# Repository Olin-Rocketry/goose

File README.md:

# G.O.O.S.E
**G**reat **O**verview **O**f **S**TM **E**lectronics

The overarching goal of this project is to establish the foundation for designing and coding boards with more advanced stm32f-series microcontrollers. These microcontrollers are arm-based, super common in industry and hobbyist projects, have a large community of support, and a ton of features avr chips don't have like:
- usb support
- real time clocks
- high clock speeds (>100Mhz)
- SDIO communication support
- debugging ports
- Direct Memory Access (DMA)

## Development Board
As a development board the primary focus is on testing new hardware (stm32, sensors, power-converts, communication lines, memory, etc). As a result, this board has a ton of pinouts for direct access to almost every pin on the stm32 and all of the communication ports. This board also has a wide voltage input range (3V3 to 14V) in order to allow for a variety of input sources (power supply, battery, usb port, etc). The following is a list of key components on the board.

- **Microcontroller**
	- STM32F401RCT6
- **Sensors**
	- IMU--BMI088
	- Magnetometer--LIS3MDLTR
	- Barometer--MS560702BA03-50
- **Non-Volatile Memory**
	- FM25L04B-G
- **Connection**
	- Micro-SD
	- Debugging/Programming Port 
	- Micro-USB
	- SPI, I2C, UART pinouts
	- Other pinouts
- **Power**
	- Input
		- 3V3 to 14V
	- Output
		- 5V (buck converter)
		- 3V3 (Low Droput Regulator)

## Schematic
The full schematic pdf view can be viewed [here](/hardware/dev_board.pdf)

## Kicad Parts & Footprints
Currently, most of the parts and footprints are located in a [personal library](https://github.com/wFairmanOlin/kicad_parts). I will transition the necessary files to the olin rocketry library when the project is closer to completion.

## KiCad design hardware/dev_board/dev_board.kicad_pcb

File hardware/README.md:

## Accessing Parts Folder 

For now, if you want to access the parts for this board, clone this [repo](https://github.com/wFairmanOlin/kicad_parts) and add a path pointing to `personal.lib` similar to this:

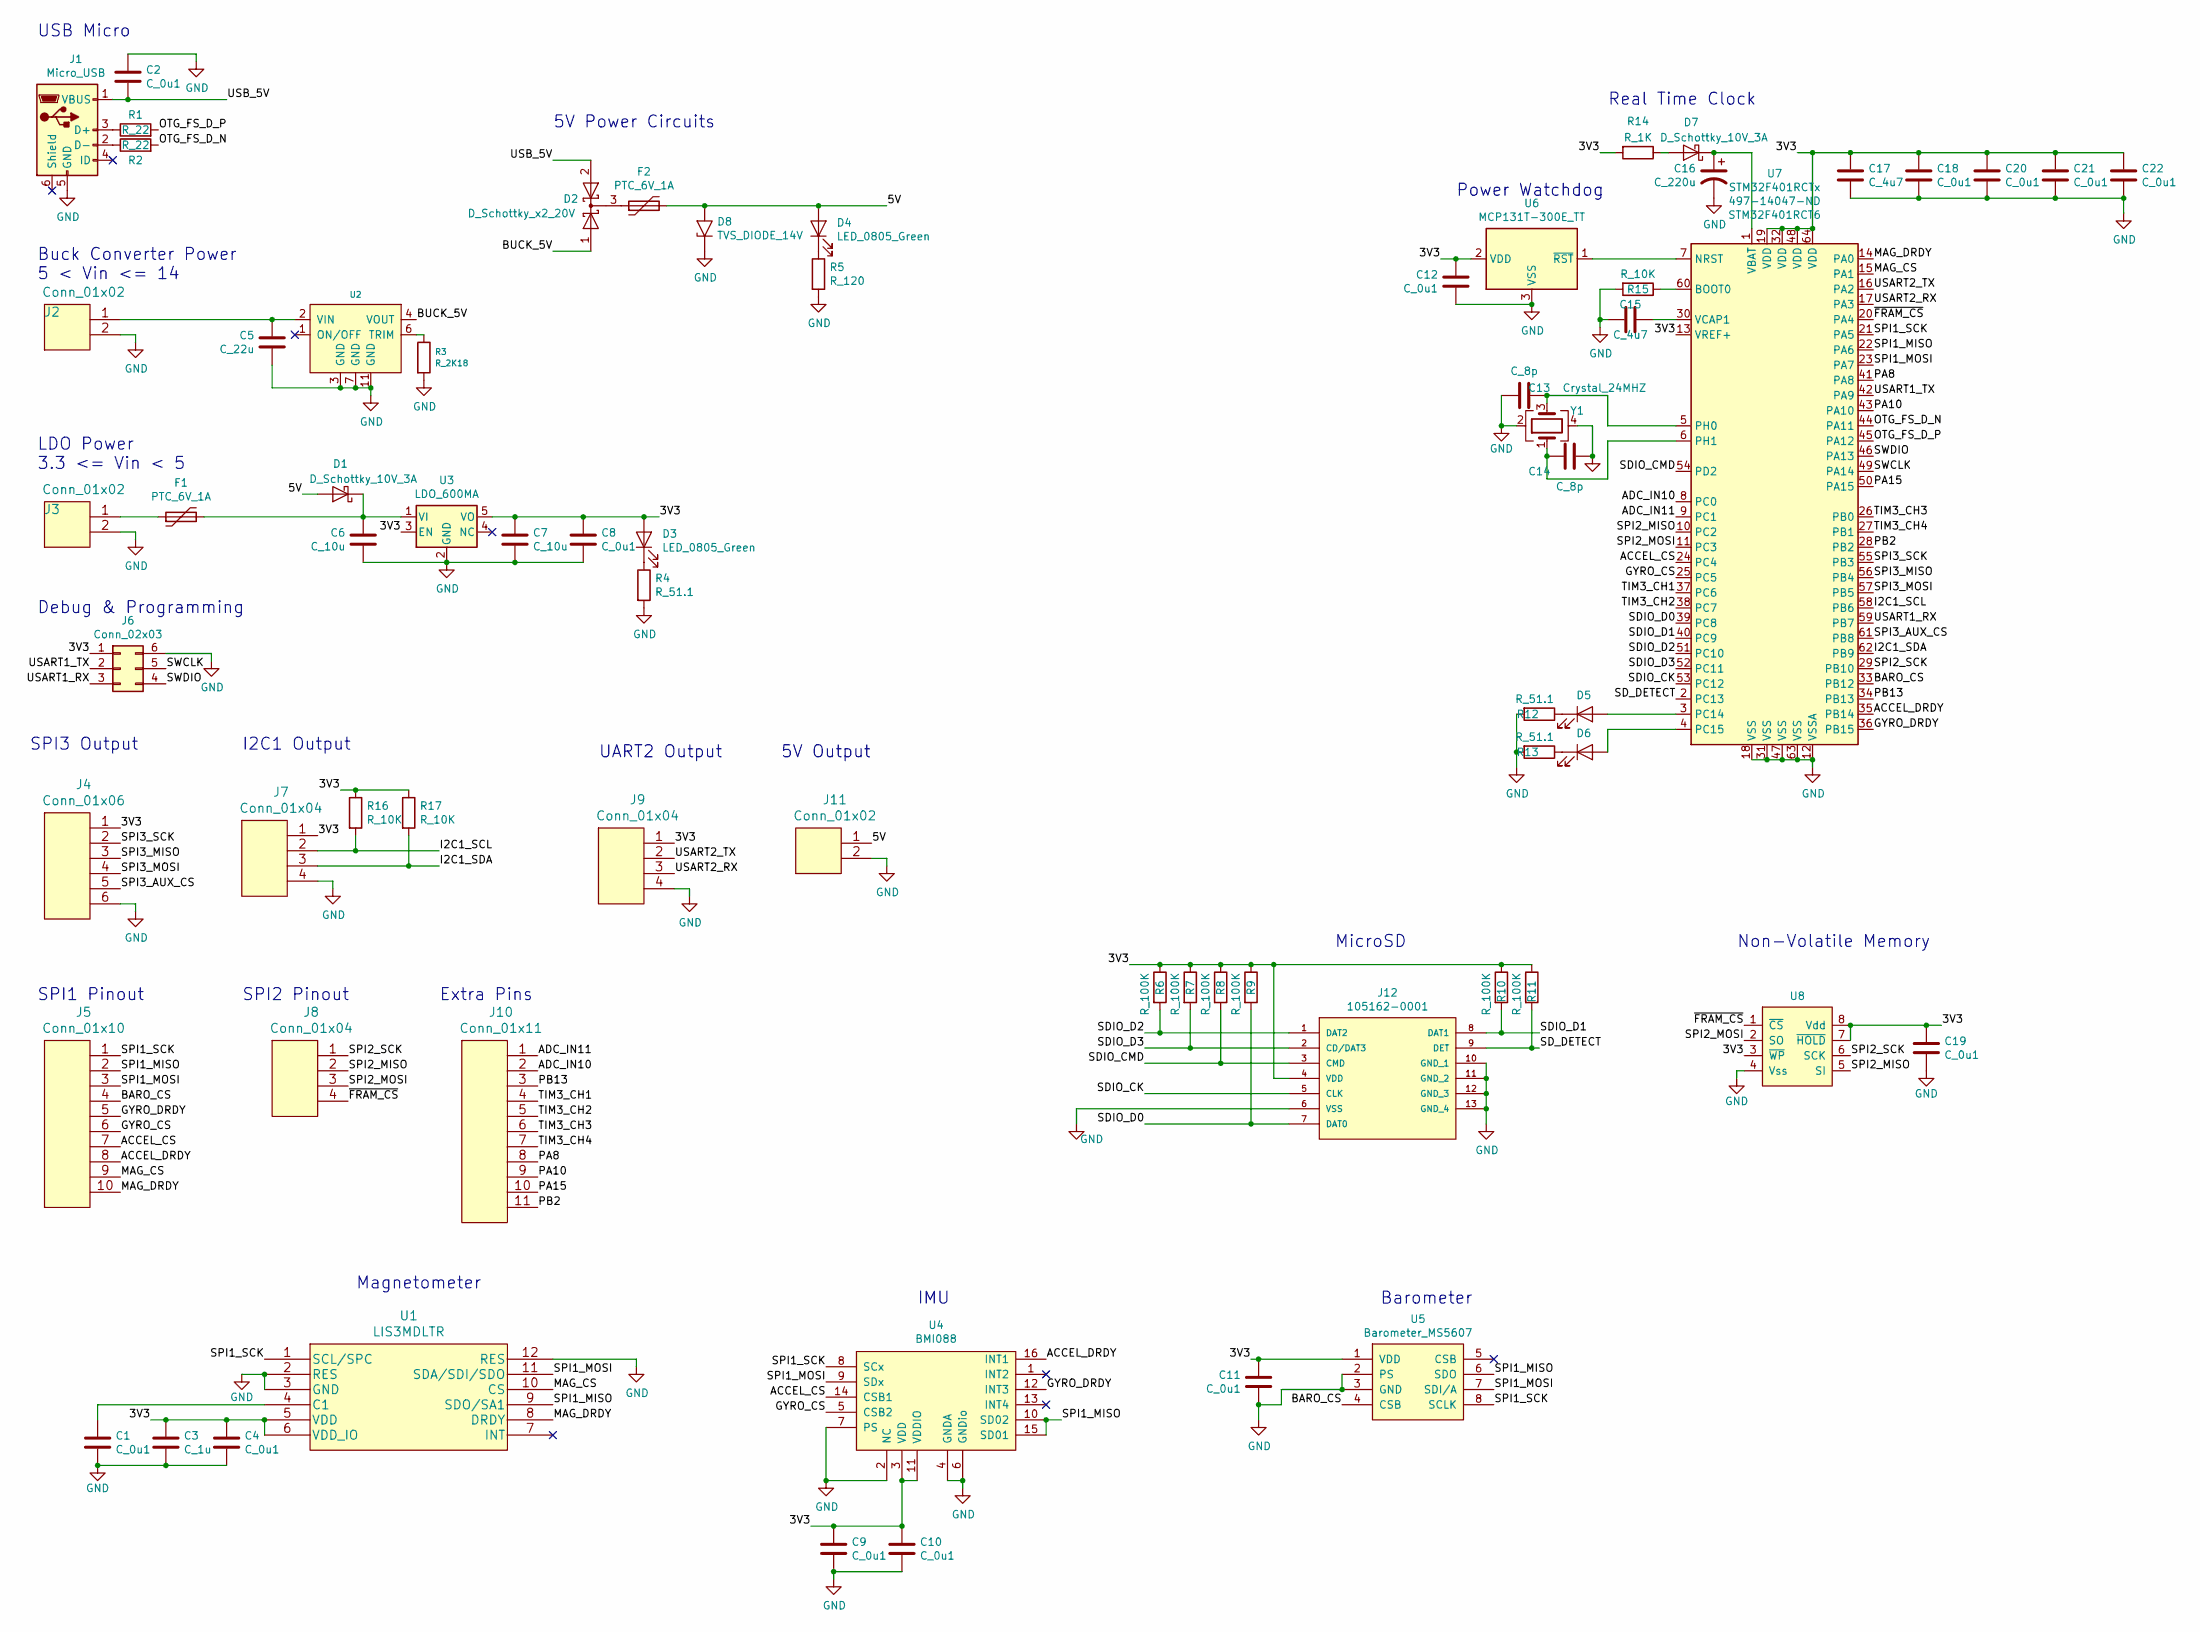
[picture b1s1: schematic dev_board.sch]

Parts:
C1, C2, C4, C8, C9, C10, C11, C12, C18, C19, C20, C21, C22: C_0u1; C_0805
C3: C_1u; C_0805
C5: C_22u; C_0805
C6, C7: C_10u; C_0805
C13, C14: C_8p; C_0805
C15, C17: C_4u7; C_0805
C16: C_220u; UWT0G221MCL6GS; MPN UWT0G221MCL6GS
D1, D7: D_Schottky_10V_3A; D_SOD-323F; MPN PMEG1030EJ,115
D2: D_Schottky_x2_20V; SOT1061; MPN PMEG2020CPA,115
D3, D4, D5, D6: LED_0805_Green; LED_0805; MPN LG R971-KN-1
D8: TVS_DIODE_14V; C_0402
F1, F2: PTC_6V_1A; R_0805_HandSoldering; MPN 0ZCK0050FF2E
J1: Micro_USB; USB_Micro-B_Molex_47346-0001
J2, J3, J11: Conn_01x02; header_01x02
J4: Conn_01x06; header_01x06
J5: Conn_01x10; header_01x10
J6: Conn_02x03; TSW-103-07-F-D; MPN TSW-103-07-F-D
J7, J8, J9: Conn_01x04; header_01x04
J10: Conn_01x11; header_01x11
J12: 105162-0001; MPN 1051620001
R1, R2: R_22; R_0805; MPN CR0805-FX-22R0ELF
R3: R_2K18; R_0805; MPN RT0805BRD072K18L
R4, R12, R13: R_51.1; R_0805; MPN RMCF0805FT51R1
R5: R_120; R_0805
R6, R7, R8, R9, R10, R11: R_100K; R_0805; MPN RC0805FR-07100KL
R14: R_1K; R_0805
R15, R16, R17: R_10K; R_0805; MPN RC0805FR-0710KL
U1: LIS3MDLTR
U2: OKL-T_1-W12P-C; OKL-T1-W12P-C; MPN OKL-T/1-W12P-C
U3: LDO_600MA; SOT-25_DIO; MPN AP7365-33WG-7
U4: BMI088
U5: Barometer_MS5607; MS561101BA03-50; MPN MS560702BA03-50
U6: MCP131T-300E_TT; SOT-23
U7: STM32F401RCTx; LQFP-64_10x10mm_Pitch0.5mm; MPN STM32F401RCT6
U8: FRAM_4K; SOIC-8_3.9x4.9mm_Pitch1.27mm; MPN FM25L04B-G
Y1: Crystal_24MHZ; NX3225SA-24.000M-STD-CSR-1; MPN NX3225SA-24.000M-STD-CSR-1

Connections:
/3V3: C3.1, C4.1, C7.1, C8.1, C9.1, C10.1, C11.2, C12.2, C17.1, C18.1, C19.1, C20.1, C21.1, C22.1, D3.2 (A), J4.1, J6.1, J7.1, J9.1, J12.4 (VDD), R6.1, R7.1, R8.1, R9.1, R10.1, R11.1, R14.2, R16.1, R17.1, U1.5 (VDD), U1.6 (VDD_IO), U3.3 (EN), U3.5 (VO), U4.3 (VDD), U4.11 (VDDIO), U5.1 (VDD), U6.2 (VDD), U7.13 (VREF+), U7.19 (VDD), U7.32 (VDD), U7.48 (VDD), U7.64 (VDD), U8.3 (~WP), U8.7 (~HOLD), U8.8 (Vdd)
/5V: D1.2 (A), D4.2 (A), D8.2 (A2), F2.2, J11.1
/ACCEL_CS: J5.7, U4.14 (CSB1), U7.24 (PC4)
/ACCEL_DRDY: J5.8, U4.16 (INT1), U7.35 (PB14)
/ADC_IN10: J10.2, U7.8 (PC0)
/ADC_IN11: J10.1, U7.9 (PC1)
/BARO_CS: J5.4, U5.4 (CSB), U7.33 (PB12)
/BUCK_5V: D2.1 (A), U2.4 (VOUT)
/GYRO_CS: J5.6, U4.5 (CSB2), U7.25 (PC5)
/GYRO_DRDY: J5.5, U4.12 (INT3), U7.36 (PB15)
/I2C1_SCL: J7.2, R16.2, U7.58 (PB6)
/I2C1_SDA: J7.3, R17.2, U7.62 (PB9)
/MAG_CS: J5.9, U1.10 (CS), U7.15 (PA1)
/MAG_DRDY: J5.10, U1.8 (DRDY), U7.14 (PA0)
/OTG_FS_D_N: R2.2, U7.44 (PA11)
/OTG_FS_D_P: R1.2, U7.45 (PA12)
/PA8: J10.8, U7.41 (PA8)
/PA10: J10.9, U7.43 (PA10)
/PA15: J10.10, U7.50 (PA15)
/PB2: J10.11, U7.28 (PB2)
/PB13: J10.3, U7.34 (PB13)
/SDIO_CK: J12.5 (CLK), U7.53 (PC12)
/SDIO_CMD: J12.3 (CMD), R8.2, U7.54 (PD2)
/SDIO_D0: J12.7 (DAT0), R9.2, U7.39 (PC8)
/SDIO_D1: J12.8 (DAT1), R10.2, U7.40 (PC9)
/SDIO_D2: J12.1 (DAT2), R6.2, U7.51 (PC10)
/SDIO_D3: J12.2 (CD/DAT3), R7.2, U7.52 (PC11)
/SD_DETECT: J12.9 (DET), R11.2, U7.2 (PC13)
/SPI1_MISO: J5.2, U1.9 (SDO/SA1), U4.10 (SD02), U4.15 (SD01), U5.6 (SDO), U7.22 (PA6)
/SPI1_MOSI: J5.3, U1.11 (SDA/SDI/SDO), U4.9 (SDx), U5.7 (SDI/A), U7.23 (PA7)
/SPI1_SCK: J5.1, U1.1 (SCL/SPC), U4.8 (SCx), U5.8 (SCLK), U7.21 (PA5)
/SPI2_MISO: J8.2, U7.10 (PC2), U8.5 (SI)
/SPI2_MOSI: J8.3, U7.11 (PC3), U8.2 (SO)
/SPI2_SCK: J8.1, U7.29 (PB10), U8.6 (SCK)
/SPI3_AUX_CS: J4.5, U7.61 (PB8)
/SPI3_MISO: J4.3, U7.56 (PB4)
/SPI3_MOSI: J4.4, U7.57 (PB5)
/SPI3_SCK: J4.2, U7.55 (PB3)
/SWCLK: J6.5, U7.49 (PA14)
/SWDIO: J6.4, U7.46 (PA13)
/TIM3_CH1: J10.4, U7.37 (PC6)
/TIM3_CH2: J10.5, U7.38 (PC7)
/TIM3_CH3: J10.6, U7.26 (PB0)
/TIM3_CH4: J10.7, U7.27 (PB1)
/USART1_RX: J6.3, U7.59 (PB7)
/USART1_TX: J6.2, U7.42 (PA9)
/USART2_RX: J9.3, U7.17 (PA3)
/USART2_TX: J9.2, U7.16 (PA2)
/USB_5V: C2.2, D2.2 (A), J1.1 (VBUS)
/~FRAM_CS: J8.4, U7.20 (PA4), U8.1 (~CS)
GND: C1.1, C2.1, C3.2, C4.2, C5.1, C6.1, C7.2, C8.2, C9.2, C10.2, C11.1, C12.1, C13.2, C14.1, C15.2, C16.2, C17.2, C18.2, C19.2, C20.2, C21.2, C22.2, D8.1 (A1), J1.5 (GND), J2.2, J3.2, J4.6, J6.6, J7.4, J9.4, J11.2, J12.6 (VSS), J12.10 (GND_1), J12.11 (GND_2), J12.12 (GND_3), J12.13 (GND_4), R3.2, R4.2, R5.2, R12.2, R13.2, R15.2, U1.2 (RES), U1.3 (GND), U1.12 (RES), U2.3 (GND), U2.7 (GND), U2.11 (GND), U3.2 (GND), U4.2 (NC), U4.4 (GNDA), U4.6 (GNDio), U4.7 (PS), U5.2 (PS), U5.3 (GND), U6.3 (VSS), U7.12 (VSSA), U7.18 (VSS), U7.31 (VSS), U7.47 (VSS), U7.63 (VSS), U8.4 (Vss), Y1.2, Y1.4
unnamed: C1.2, U1.4 (C1)
unnamed: C5.2, J2.1, U2.2 (VIN)
unnamed: C6.2, D1.1 (K), F1.2, U3.1 (VI)
unnamed: C13.1, U7.5 (PH0), Y1.3
unnamed: C14.2, U7.6 (PH1), Y1.1
unnamed: C15.1, U7.30 (VCAP1)
unnamed: C16.1, D7.1 (K), U7.1 (VBAT)
unnamed: D2.3 (K), F2.1
unnamed: D3.1 (K), R4.1
unnamed: D4.1 (K), R5.1
unnamed: D5.1 (K), R12.1
unnamed: D5.2 (A), U7.3 (PC14)
unnamed: D6.1 (K), R13.1
unnamed: D6.2 (A), U7.4 (PC15)
unnamed: D7.2 (A), R14.1
unnamed: F1.1, J3.1
unnamed: J1.2 (D-), R2.1
unnamed: J1.3 (D+), R1.1
unnamed: R3.1, U2.6 (TRIM)
unnamed: R15.1, U7.60 (BOOT0)
unnamed: U6.1 (~RST), U7.7 (NRST)

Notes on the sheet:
Buck Converter Power 5 < Vin <= 14
USB Micro
LDO Power 3.3 <= Vin < 5
Debug & Programming
5V Power Circuits
SPI3 Output
I2C1 Output
UART2 Output
Magnetometer
IMU
Barometer
MicroSD
Non-Volatile Memory
SPI1 Pinout
SPI2 Pinout
Power Watchdog
Real Time Clock
5V Output
Extra Pins

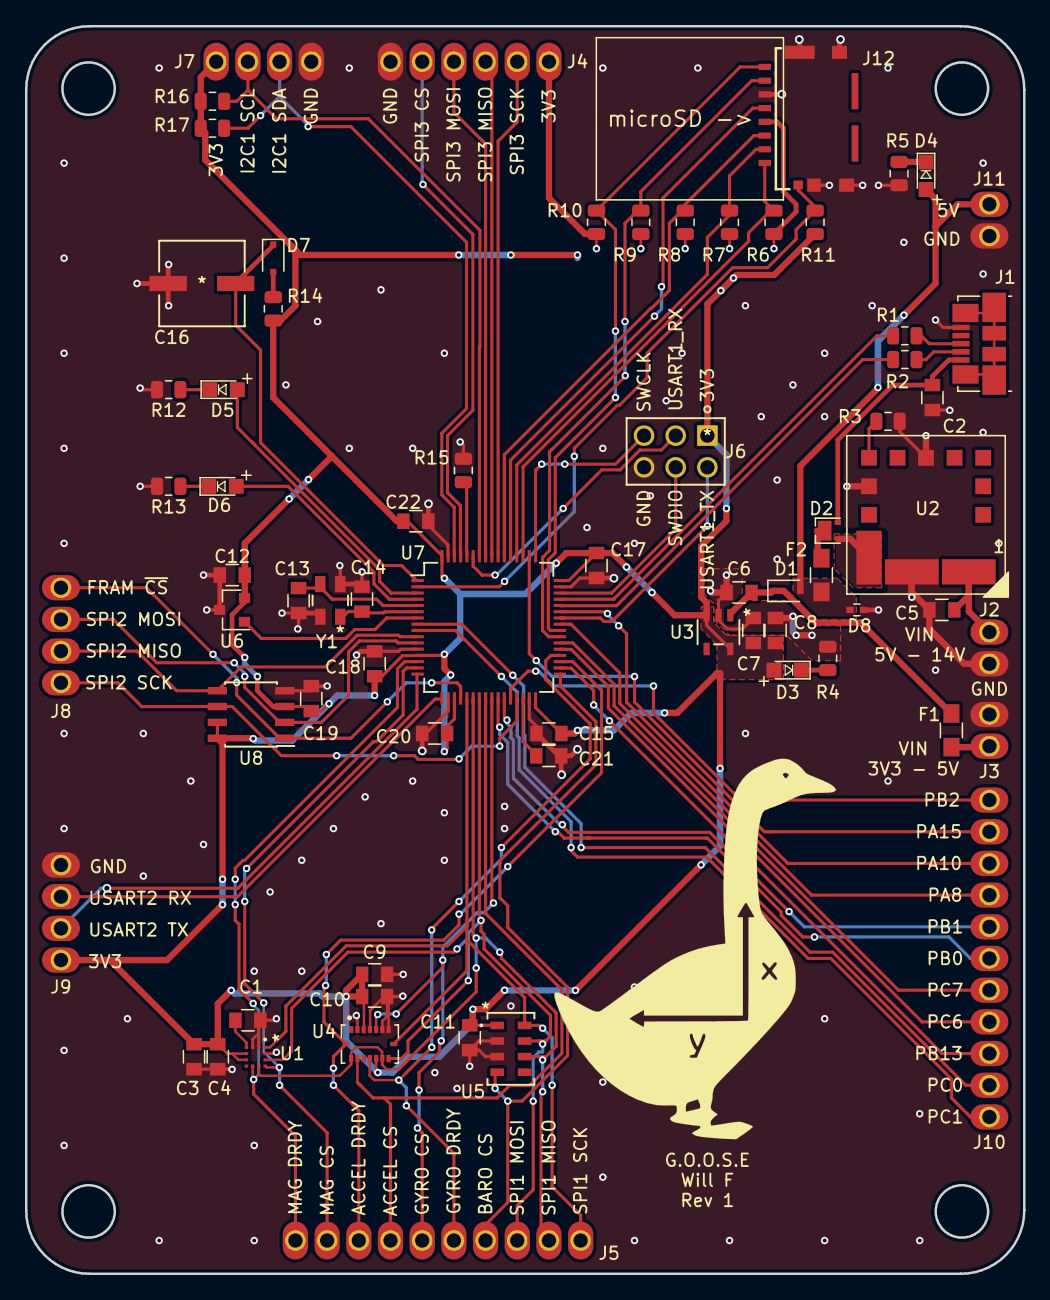
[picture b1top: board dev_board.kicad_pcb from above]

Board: 2 copper layers, 80.0 x 100.0 mm, 70 parts (0 on the bottom side), 72 nets.

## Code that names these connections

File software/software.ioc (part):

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Mcu.Name=STM32F401R(B-C)Tx
Mcu.Package=LQFP64
Mcu.UserName=STM32F401RCTx
PA0-WKUP.Signal=GPIO_Input
PA1.Signal=GPIO_Output
PA11.Mode=Device_Only
PA11.Signal=USB_OTG_FS_DM
PA12.Mode=Device_Only
PA12.Signal=USB_OTG_FS_DP
PA13.Mode=Serial_Wire
PA13.Signal=SYS_JTMS-SWDIO
PA14.Mode=Serial_Wire
PA14.Signal=SYS_JTCK-SWCLK
PA2.Mode=Asynchronous
PA2.Signal=USART2_TX
PA3.Mode=Asynchronous
PA3.Signal=USART2_RX
PA4.Signal=GPIO_Output
PA5.Mode=Full_Duplex_Master
PA5.Signal=SPI1_SCK
PA6.Mode=Full_Duplex_Master
PA6.Signal=SPI1_MISO
PA7.Mode=Full_Duplex_Master
PA7.Signal=SPI1_MOSI
PA9.Mode=Asynchronous
PA9.Signal=USART1_TX
PB0.Signal=S_TIM3_CH3
PB1.Signal=S_TIM3_CH4
PB10.Mode=Full_Duplex_Master
PB10.Signal=SPI2_SCK
PB12.Signal=GPIO_Output
PB14.Signal=GPIO_Input
PB15.Signal=GPIO_Input
PB3.Mode=Full_Duplex_Master
PB3.Signal=SPI3_SCK
PB4.Mode=Full_Duplex_Master
PB4.Signal=SPI3_MISO
PB5.Mode=Full_Duplex_Master
PB5.Signal=SPI3_MOSI
PB6.Mode=I2C
PB6.Signal=I2C1_SCL
PB7.Mode=Asynchronous
PB7.Signal=USART1_RX
PB8.Signal=GPIO_Output
PB9.Mode=I2C
PB9.Signal=I2C1_SDA
PC0.Signal=ADCx_IN10
PC1.Signal=ADCx_IN11
PC10.Mode=SD_4_bits_Wide_bus
PC10.Signal=SDIO_D2
PC11.Mode=SD_4_bits_Wide_bus
PC11.Signal=SDIO_D3
PC12.Mode=SD_4_bits_Wide_bus
PC12.Signal=SDIO_CK
PC13-ANTI_TAMP.Signal=GPIO_Input
PC14-OSC32_IN.Signal=GPIO_Output
PC15-OSC32_OUT.Signal=GPIO_Output
PC2.Mode=Full_Duplex_Master
PC2.Signal=SPI2_MISO
PC3.Mode=Full_Duplex_Master
PC3.Signal=SPI2_MOSI
PC4.Signal=GPIO_Output
PC5.Signal=GPIO_Output
PC6.Signal=S_TIM3_CH1
PC7.Signal=S_TIM3_CH2
PC8.Mode=SD_4_bits_Wide_bus
PC8.Signal=SDIO_D0
PC9.Mode=SD_4_bits_Wide_bus
PC9.Signal=SDIO_D1
PD2.Mode=SD_4_bits_Wide_bus
PD2.Signal=SDIO_CMD
PH0\ -\ OSC_IN.Mode=HSE-External-Oscillator
PH0\ -\ OSC_IN.Signal=RCC_OSC_IN
PH1\ -\ OSC_OUT.Mode=HSE-External-Oscillator
PH1\ -\ OSC_OUT.Signal=RCC_OSC_OUT
RCC.HSE_VALUE=24000000
RCC.SYSCLKFreq_VALUE=16000000
board=custom

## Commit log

2021-02-19 added folders and created kicad project
2021-02-21 finished schematic
2021-02-21 Fixed a few errors
2021-02-21 fixed power issue with schematic
2021-02-24 added the all important axis guide and started layout
2021-03-07 finished layout
2021-03-07 added more vias
2021-03-24 added fabrication files
2021-03-24 deleted excess file
2021-03-24 added csv

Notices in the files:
parts and their libraries:
Copyright 2016 Accelerated Designs. All rights reserved.
